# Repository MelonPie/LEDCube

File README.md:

# Introduction

Heya and happy bday to you. I was thinking for a long time what I can possibly gift to you and came up with a 
soldering challenge. It had to be something where you have to notice every poor solder spot every time you look at 
it. What could be better for this purpose than a LED cube. I searched through some kits, but they were all just 
not good enough, so I designed one of my own. When you are finished there would be only two of those in the whole 
world (I assembled one as well in order to test if I did any mistakes but no. First try babyyy xD ).

The cube itself is built around an [ESP32](https://www.az-delivery.de/en/products/esp32-developmentboard) Devboard. 
Every LED cube layer has a common cathode. The anodes of an arbitrary LED are connected through all the 
layers. The percepted image is built by building one layer configuration followed by the enablement of the same with 
the common cathode. After some time the cathode is disabled and the next layer is encoded. This happens for every 
layer. The encoding of the layer is done via the [74HC595](https://www.sparkfun.com/datasheets/IC/SN74HC595.pdf) 
shift registers (IC2, IC3). Each shift register encodes a half of the layer. The curently selected layer is 
determined by enabling the common layer cathode with the [ULN2003](https://en.wikipedia.org/wiki/ULN2003A)(IC1).

Additionally, there are two buttons which use the ESP32 DevBoards builtin pullup resistors to get a logical LOW when 
pressed and a HIGH signal otherwise.

# Partslist
 - 64x LEDs blue diffuse 
 - Blank wire
 - 1x ESP32 devboard
 - 2x cutable female pin header for the esp32
 - 16x Resistors 100 Ohm
 - 2x 74HC595N
 - 1x ULN2003
 - 3x DIL-IC 16 pin sockets (optional)
 - 2x Buttons
 - 1x pin header 3 pins
 - 1x pin header connector 2 pin
 - 1x PCB
 - 4x PCB separator
 - 4x PCB separator screw flat head
 - 4x PCB separator screw cylinder head

 I put some extra parts in the package just to be sure
# Cube
This chapter is a guide how to build the actual LED cube. If you feel adventurous you can do as you like, but I 
found the described methods to work the best for me.

Pleae note there are 4 screw holes on the corners of the PCB. The print indicates which site is the parts should be 
mounted on. At the end the LED cube and the buttons shold be on top site and the other components on the bottom site 
of the PCB. ount the PCB separators on the back like shown in the image below. Please note that the flathead screws 
are used to fasten the separators to the PCB.

## Building layers
Before soldering any oter parts it is best to build the cube first. Note that there are additional holes in the pcb 
just in the right diameter to stick LEDs in them. Coincidence? However we can use those to get the spacing between 
the LEDs right. First let prepare the LEDs for the first layer.

Place a LED in one of the holes and align it to the hole verticaly from it like indicated with the green line in the 
image below. Be aware of the anode and cathode indicated by the length of the component feet. Then bend the cathode 
(which is indicated by a K because I was thinking in German when I made this image ^^;) towards the hole diagonally 
from it like shown in the following image. Repeat for 13 LEDs. I will call them LED_A from now on.

Next bend the cathodes of the other 3 LEDs like shown in the following image. Those are called LED_B.

For the first line start with the bottom line and solder all the cathodes together like shown in this image. Note 
that only LED_As are used in this step 

To start the second row use LED_B and bend the cathode leg tip like shown in the image below (red). Then connect one 
of the LED_A (purle) legs. Continue the row in the same manner like done in the first row.

Use the blank wire to connect all the rows perpendicularly like shown here.

At this point I would strongly recommend to test if all the LEDs survived the solder, by applying a low voltage ~1V 
to every LED. (Maybe with a new power supply you got recently by any chance ;) ).  

Repeat all the steps from this chapter until you have four layers.

## Connecting layers

Next step is to connect all four layers to the final cube. The main challenge here is to get the distance even 
between the layers. Remember we are building a cube not a trapeze or a parallelogram. In the image below I used a 
toilet paper roll  to separate the layers by cutting 2cm high segments out of it. Those can be removed fairly easy 
by pulling them to the side.

Finally test if all the LEDs are working properly by applying a low voltage like before.

# Board
Below is an see through image of the board. Solder all the components like ilustrated here. Note that the ICs and IC 
sockets have an orientation indicated by the cutout on their sites. The orientation of the ESP32 board is given by 
the antena (Antena should be on the outer side of the board and the usb port should be directed towards IC3). The 
buttons should be attached on the front side of the board alongside with the freshly made LED cube  

After the components are attached solder the common cathodes of the respective layers to JP21. Please note I used 
connectors on the image below because it was my first build and I wasn't sure if it's going to work. I used the pin 
headers which are also used to attach the ESP32 and cut them in single sockets for the anodes and used a line of 5 
to attach the corner anode and the four common cathodes. However, you can solder the LED cube directly to the PCB. 

That's it. If you power on the cube by attaching the micro-usb cable it should start with the first animation made 
specialy for you :D. You can switch through various animations by pressing S1 (S2 does not have any function at this 
point). 

# Flashing

I flashed the devboard before shipping so it is ready to go if you did everything right. However, if you want to 
experiment with it I attached it to this repo in the directory `src`. To flash the microcontroller I used [Arduino 
studio](https://www.arduino.cc/en/software). The board used in this project is not a part of the default 
library but can be imported by adding the board manager uri `http://arduino.esp8266.
com/stable/package_esp8266com_index.json` to the preferences. Below is the configuration I used.

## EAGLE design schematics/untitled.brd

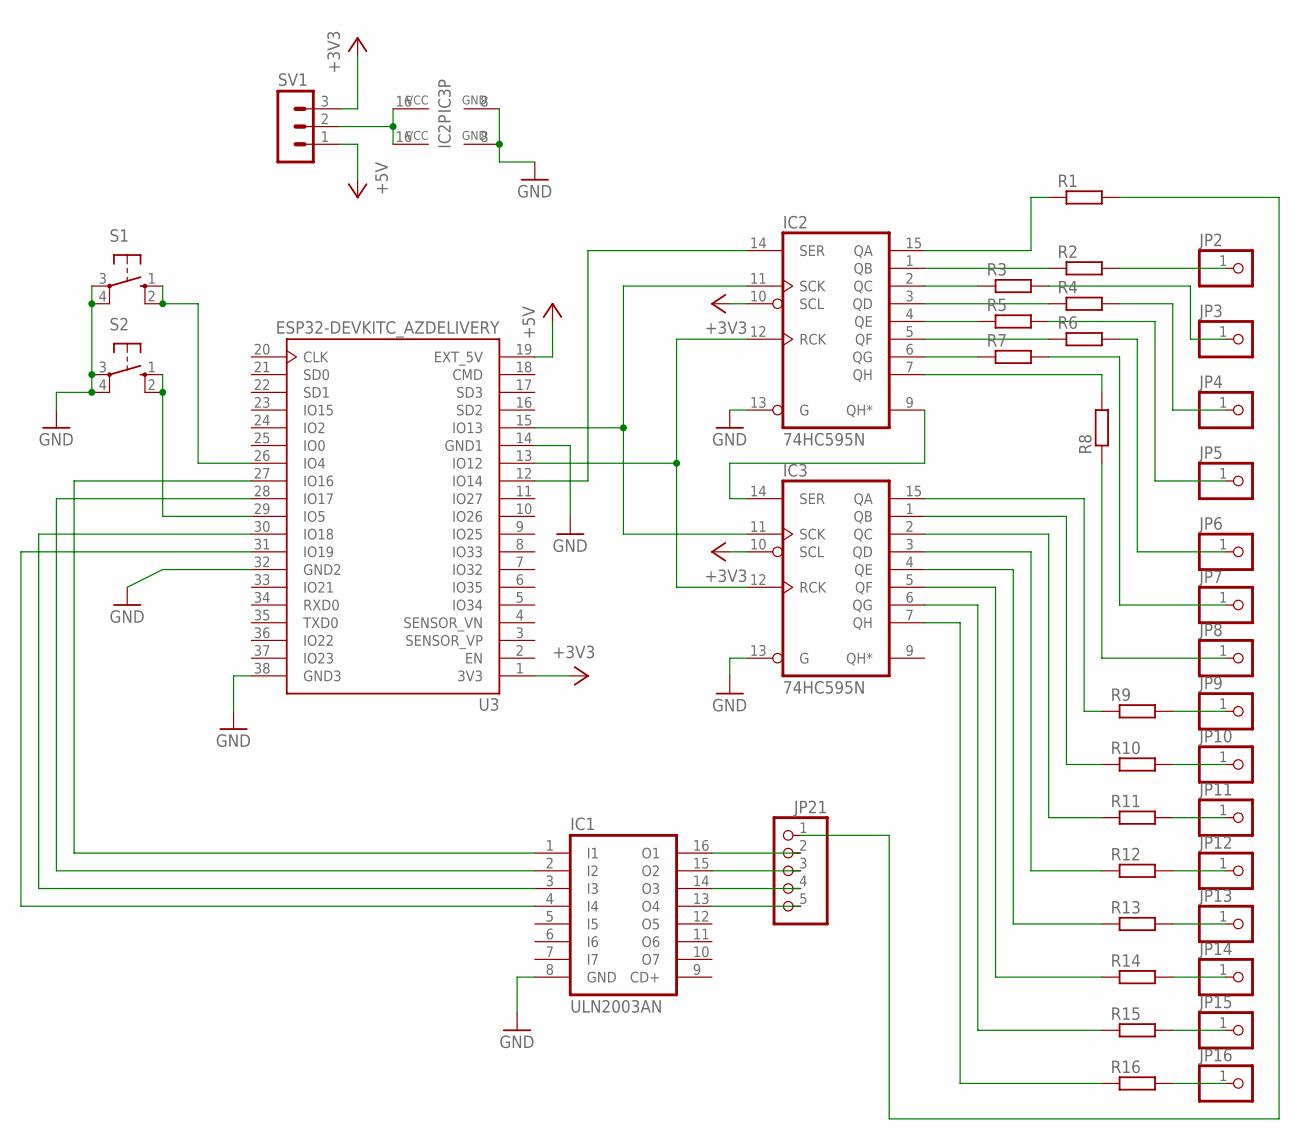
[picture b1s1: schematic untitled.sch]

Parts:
IC1: ULN2003AN; DIL16
IC2, IC3: 74HC595N; DIL16
JP2, JP3, JP4, JP5, JP6, JP7, JP8, JP9, JP10, JP11, JP12, JP13, JP14, JP15, JP16: PINHD-1X1; 1X01
JP21: PINHD-1X5; 1X05
R1, R2, R3, R4, R5, R6, R7, R8, R9, R10, R11, R12, R13, R14, R15, R16: R-EU_0207/10; 0207/10
S1, S2: 10-XX; B3F-10XX
SV1: MA03-1
U3: ESP32-DEVKITC_AZDELIVERY; FP_ESP32-DEVKIT_AZDELIVERY

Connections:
+3V3: IC2.10 (SCL), IC3.10 (SCL), SV1.3, U3.1 (3V3)
+5V: SV1.1, U3.19 (EXT_5V)
GND: IC1.8 (GND), IC2.8 (GND), IC2.13 (G), IC3.8 (GND), IC3.13 (G), S1.3, S1.4 (P1), S2.3, S2.4 (P1), U3.14 (GND1), U3.32 (GND2), U3.38 (GND3)
unnamed: IC2.11 (SCK), IC3.11 (SCK), U3.15 (IO13)
unnamed: IC2.12 (RCK), IC3.12 (RCK), U3.13 (IO12)
unnamed: IC2.14 (SER), U3.12 (IO14)
unnamed: IC2.9 (QH*), IC3.14 (SER)
unnamed: JP21.1, R1.2
unnamed: IC1.16 (O1), JP21.2
unnamed: IC1.15 (O2), JP21.3
unnamed: IC1.14 (O3), JP21.4
unnamed: IC2.15 (QA), R1.1
unnamed: IC2.1 (QB), R2.1
unnamed: JP3.1, R3.2
unnamed: JP4.1, R4.2
unnamed: JP5.1, R5.2
unnamed: JP6.1, R6.2
unnamed: JP7.1, R7.2
unnamed: JP8.1, R8.1
unnamed: IC3.15 (QA), R9.1
unnamed: IC3.1 (QB), R10.1
unnamed: IC3.2 (QC), R11.1
unnamed: IC3.3 (QD), R12.1
unnamed: IC3.4 (QE), R13.1
unnamed: IC3.5 (QF), R14.1
unnamed: IC3.6 (QG), R15.1
unnamed: IC3.7 (QH), R16.1
unnamed: IC1.1 (I1), U3.27 (IO16)
unnamed: IC1.2 (I2), U3.28 (IO17)
unnamed: IC1.3 (I3), U3.30 (IO18)
unnamed: IC1.4 (I4), U3.31 (IO19)
unnamed: S1.1 (S), S1.2 (S1), U3.26 (IO4)
unnamed: S2.1 (S), S2.2 (S1), U3.29 (IO5)
unnamed: IC1.13 (O4), JP21.5
unnamed: JP2.1, R2.2
unnamed: IC2.2 (QC), R3.1
unnamed: IC2.3 (QD), R4.1
unnamed: IC2.4 (QE), R5.1
unnamed: IC2.5 (QF), R6.1
unnamed: IC2.6 (QG), R7.1
unnamed: IC2.7 (QH), R8.2
unnamed: JP9.1, R9.2
unnamed: JP10.1, R10.2
unnamed: JP11.1, R11.2
unnamed: JP12.1, R12.2
unnamed: JP13.1, R13.2
unnamed: JP14.1, R14.2
unnamed: JP15.1, R15.2
unnamed: JP16.1, R16.2
unnamed: IC2.16 (VCC), IC3.16 (VCC), SV1.2

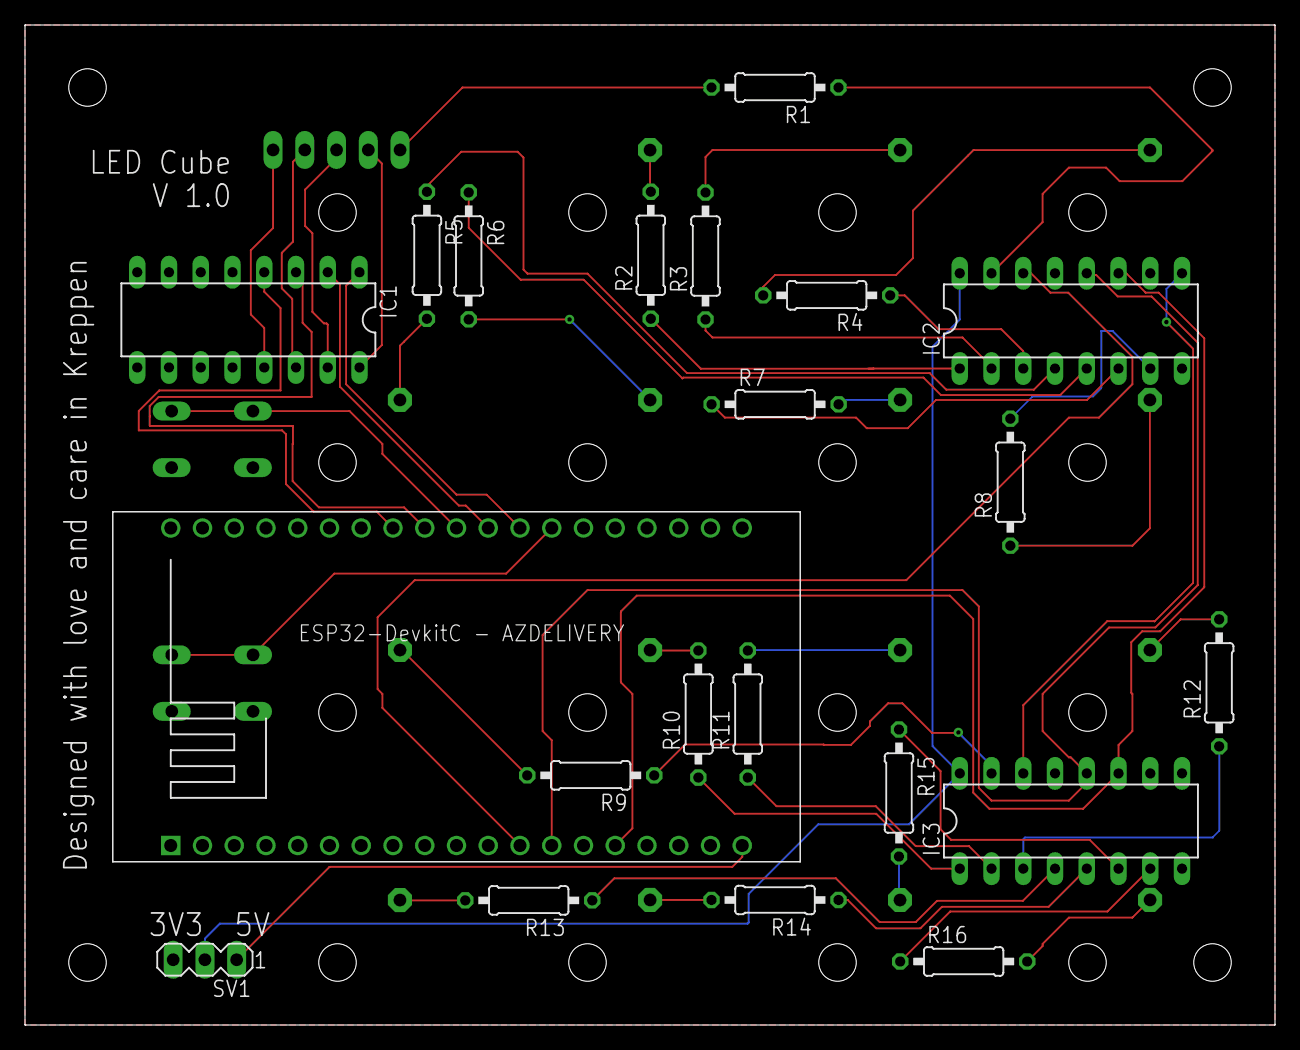
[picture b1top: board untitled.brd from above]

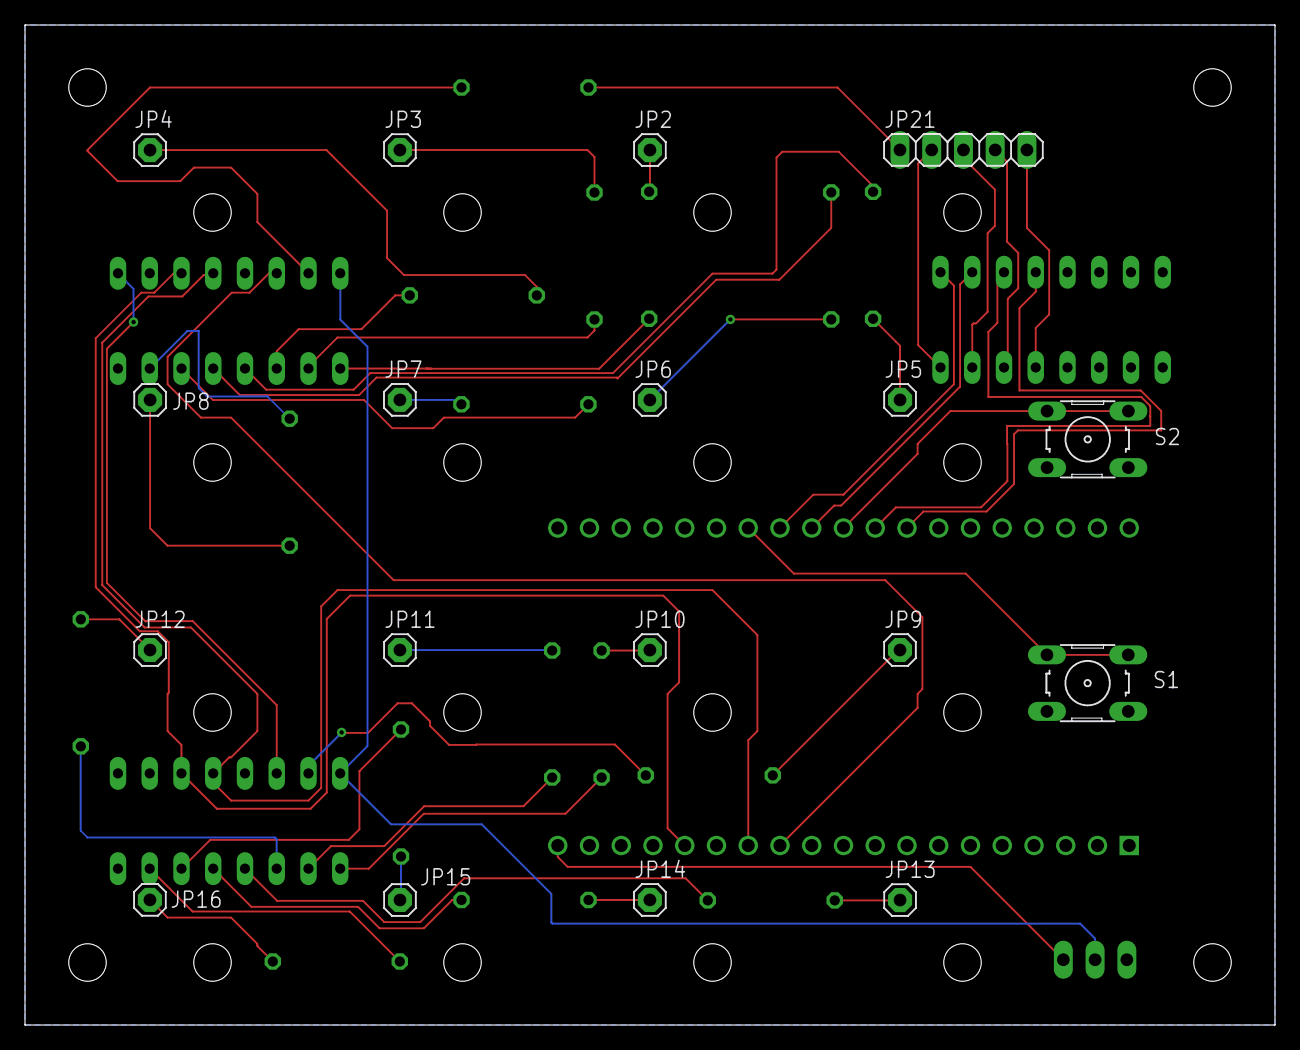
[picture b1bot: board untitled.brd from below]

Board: 2 copper layers, 100.0 x 80.0 mm, 39 parts (18 on the bottom side), 50 nets.

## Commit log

2023-12-04 started Readme
2023-12-04 images
2023-12-05 finished readme for now
2023-12-05 removed idea dir
